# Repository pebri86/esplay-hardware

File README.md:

# esplay-hardware
ESP32 Device which can emulate game and other purpose, has display, button input, sdcard slot, built-in li-ion charger, pcm 5102 DAC module.

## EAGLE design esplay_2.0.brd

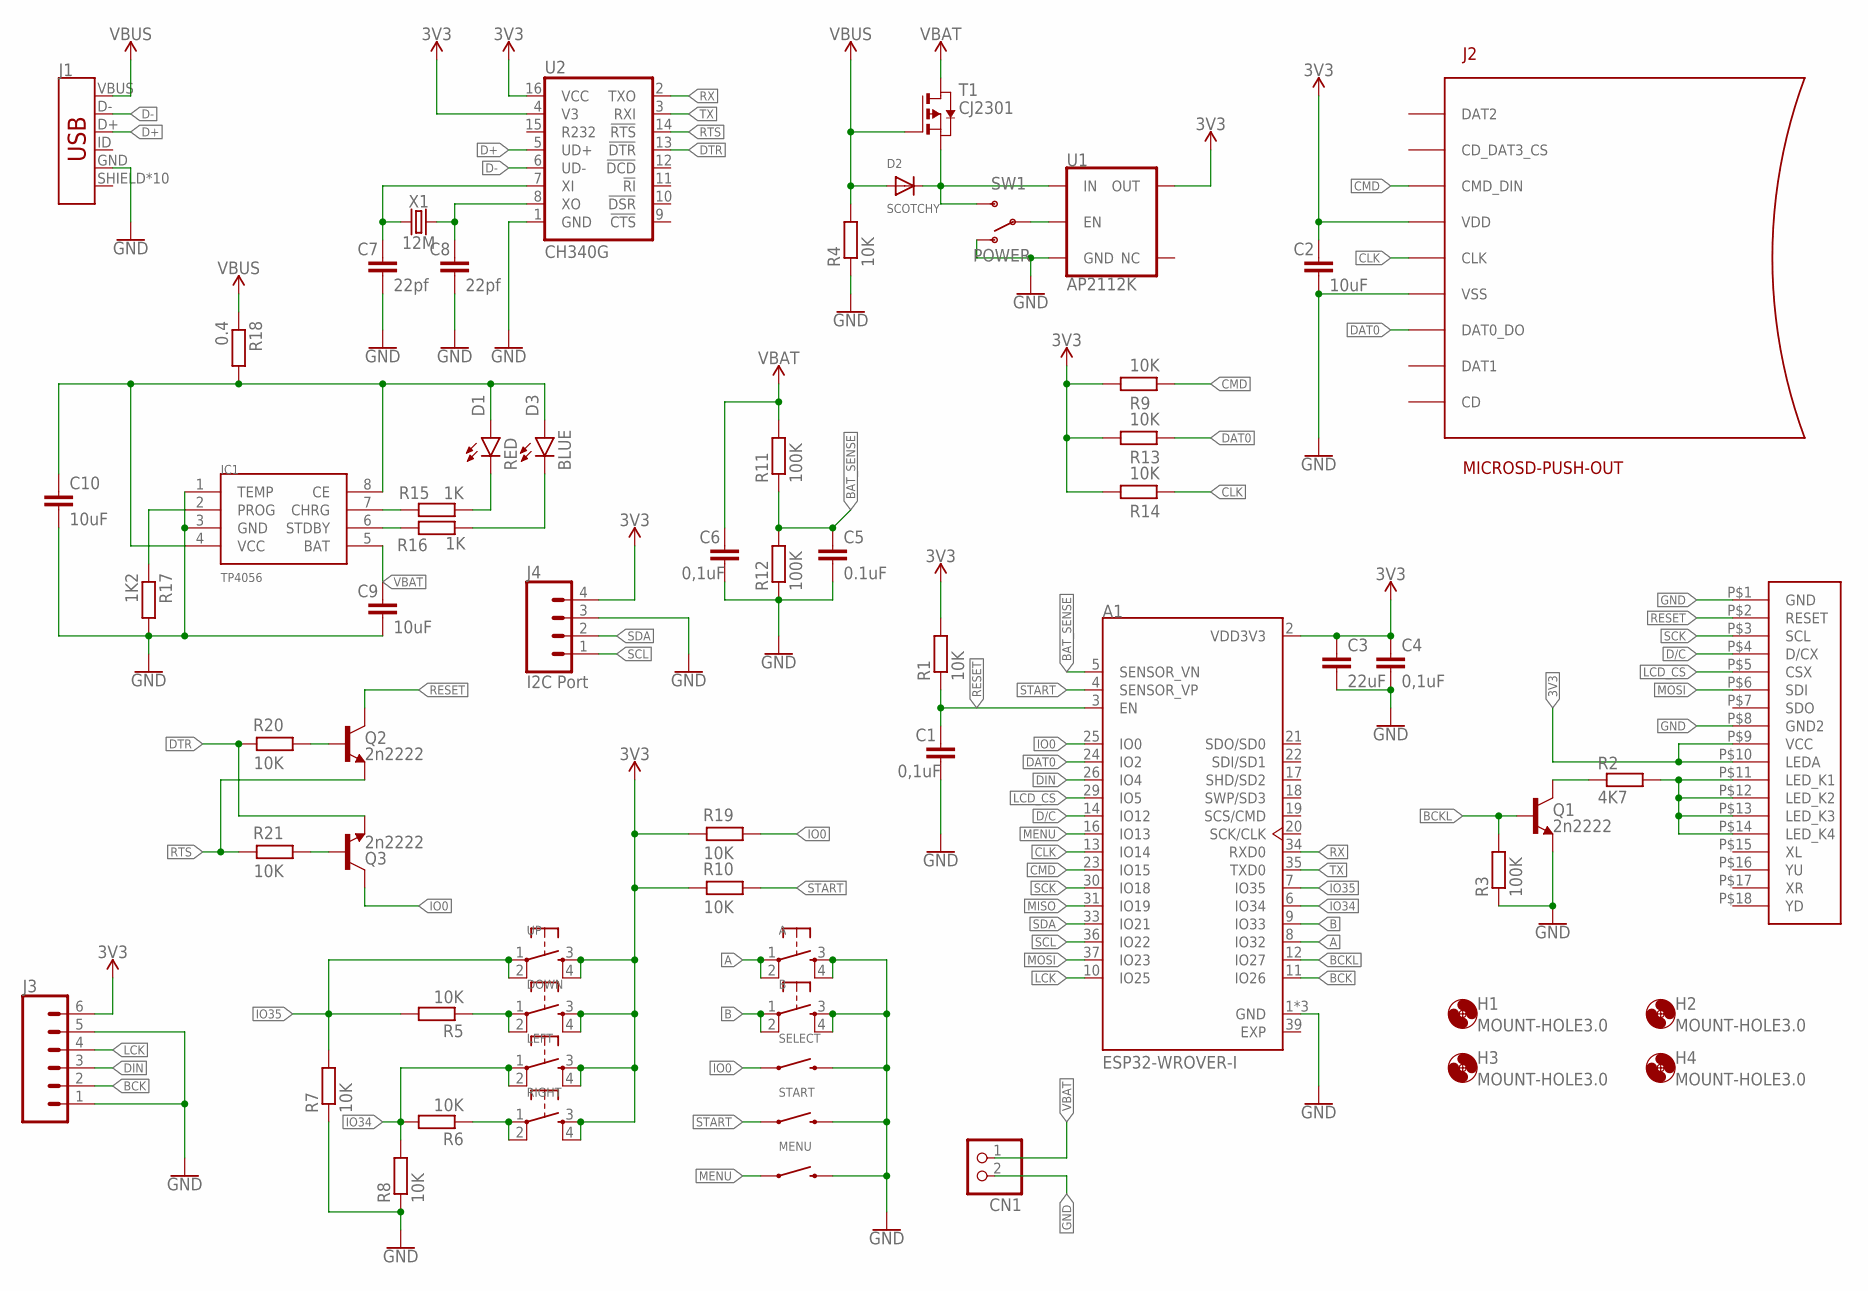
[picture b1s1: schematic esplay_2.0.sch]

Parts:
A: MOMENTARY-SWITCH-SPST-2-SMD-5.2MM; TACTILE_SWITCH_SMD_5.2MM
A1: ESP32-WROVER-I; XCVR_ESP32-WROVER-I
B: MOMENTARY-SWITCH-SPST-2-SMD-5.2MM; TACTILE_SWITCH_SMD_5.2MM
C1, C4, C6: 0,1uF; C0805
C2, C9, C10: 10uF; C0805
C3: 22uF; C0805
C5: 0.1uF; C0805
C7, C8: 22pf; C0805
CN1: JST_2PIN-SMT-RA; JST-PH-2-SMT-RA
D1: RED; LED-0603
D2: SCOTCHY; SMADIODE
D3: BLUE; LED-0603
DOWN: MOMENTARY-SWITCH-SPST-2-SMD-5.2MM; TACTILE_SWITCH_SMD_5.2MM
H1, H2, H3, H4: MOUNT-HOLE3.0; 3,0
IC1: TP4056; SOP-8
J1: USB_MICRO-B_HALF_PTH_MILL; USB-MICROB-PTH-MILL
J2: MICROSD-PUSH-OUT
J3: CONN_06LOCK; 1X06_LOCK
J4: I2C Port; JST-4-PTH
LEFT: MOMENTARY-SWITCH-SPST-2-SMD-5.2MM; TACTILE_SWITCH_SMD_5.2MM
MENU: MOMENTARY-SWITCH-SPST-SMD-6.0X3.5MM; TACTILE_SWITCH_SMD_6.0X3.5MM
Q1, Q2, Q3: 2n2222; SOT23-3
R1, R4, R5, R6, R7, R8, R9, R10, R13, R14, R19, R20, R21: 10K; R0805
R2: 4K7; R0805
R3, R11, R12: 100K; R0805
R15, R16: 1K; R0805
R17: 1K2; R0805
R18: 0.4; R0805
RIGHT: MOMENTARY-SWITCH-SPST-2-SMD-5.2MM; TACTILE_SWITCH_SMD_5.2MM
SELECT: MOMENTARY-SWITCH-SPST-SMD-6.0X3.5MM; TACTILE_SWITCH_SMD_6.0X3.5MM
START: MOMENTARY-SWITCH-SPST-SMD-6.0X3.5MM; TACTILE_SWITCH_SMD_6.0X3.5MM
SW1: POWER; KPS-1290
T1: CJ2301; SOT-23
TFT_DISPLAY: ILI9341-2.4
U1: AP2112K; SOT23-5
U2: CH340G; SO016
UP: MOMENTARY-SWITCH-SPST-2-SMD-5.2MM; TACTILE_SWITCH_SMD_5.2MM
X1: 12M; CRYSTAL-SMD-2X6-CYL

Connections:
3V3: A1.2 (VDD3V3), C2.1, C3.1, C4.1, DOWN.3, DOWN.4, J2.4 (VDD), J3.6, J4.4, LEFT.3, LEFT.4, R1.2, R9.1, R10.2, R13.1, R14.1, R19.2, RIGHT.3, RIGHT.4, TFT_DISPLAY.P$9 (VCC), TFT_DISPLAY.P$10 (LEDA), U1.5 (OUT), U2.4 (V3), U2.16 (VCC), UP.3, UP.4
A: A.1, A.2, A1.8 (IO32)
B: A1.9 (IO33), B.1, B.2
BAT_SENSE: A1.5 (SENSOR_VN), C5.1, R11.1, R12.2
BCK: A1.11 (IO26), J3.2
BCKL: A1.12 (IO27), Q1.1 (B), R3.2
CLK: A1.13 (IO14), J2.5 (CLK), R14.2
CMD: A1.23 (IO15), J2.3 (CMD_DIN), R9.2
D+: J1.D+, U2.5 (UD+)
D-: J1.D-, U2.6 (UD-)
D/C: A1.14 (IO12), TFT_DISPLAY.P$4 (D/CX)
DAT0: A1.24 (IO2), J2.7 (DAT0_DO), R13.2
DIN: A1.26 (IO4), J3.3
DTR: Q3.2 (E), R20.2, U2.13 (!DTR)
EXP: A1.39 (EXP)
GND: A.3, A.4, A1.1 (GND), A1.15 (GND), A1.38 (GND), B.3, B.4, C1.2, C2.2, C3.2, C4.2, C5.2, C6.2, C7.2, C8.2, C9.2, C10.2, CN1.2 (1), IC1.1 (TEMP), IC1.3 (GND), J1.GND, J2.6 (VSS), J2.G1 (VSS), J2.G2 (VSS), J2.G3 (VSS), J2.G4 (VSS), J3.1, J3.5, J4.3, MENU.2, Q1.2 (E), R3.1, R4.1, R7.1, R8.1, R12.1, R17.2, SELECT.2, START.2, SW1.O, TFT_DISPLAY.P$1 (GND), TFT_DISPLAY.P$8 (GND2), U1.2 (GND), U2.1 (GND)
IO0: A1.25 (IO0), Q3.3 (C), R19.1, SELECT.1
IO34: A1.6 (IO34), LEFT.1, LEFT.2, R6.2, R8.2
IO35: A1.7 (IO35), R5.2, R7.2, UP.1, UP.2
LCD_CS: A1.29 (IO5), TFT_DISPLAY.P$5 (CSX)
LCK: A1.10 (IO25), J3.4
MENU: A1.16 (IO13), MENU.1
MISO: A1.31 (IO19)
MOSI: A1.37 (IO23), TFT_DISPLAY.P$6 (SDI)
unnamed: D2.C, SW1.S, T1.2 (S), U1.1 (IN)
unnamed: R2.2, TFT_DISPLAY.P$11 (LED_K1), TFT_DISPLAY.P$12 (LED_K2), TFT_DISPLAY.P$13 (LED_K3), TFT_DISPLAY.P$14 (LED_K4)
unnamed: SW1.P, U1.3 (EN)
unnamed: Q1.3 (C), R2.1
unnamed: C7.1, U2.7 (XI), X1.X1 (1)
unnamed: C8.1, U2.8 (XO), X1.X2 (2)
unnamed: R6.1, RIGHT.1, RIGHT.2
unnamed: DOWN.1, DOWN.2, R5.1
unnamed: IC1.2 (PROG), R17.1
unnamed: IC1.7 (CHRG), R15.2
unnamed: IC1.6 (STDBY), R16.2
unnamed: D1.C, R15.1
unnamed: D3.C, R16.1
unnamed: C10.1, D1.A, D3.A, IC1.4 (VCC), IC1.8 (CE), R18.2
unnamed: Q2.1 (B), R20.1
unnamed: Q3.1 (B), R21.1
RESET: A1.3 (EN), C1.1, Q2.3 (C), R1.1, TFT_DISPLAY.P$2 (RESET)
RTS: Q2.2 (E), R21.2, U2.14 (!RTS)
RX: A1.34 (RXD0), U2.2 (TXO)
SCK: A1.30 (IO18), TFT_DISPLAY.P$3 (SCL)
SCL: A1.36 (IO22), J4.1
SDA: A1.33 (IO21), J4.2
START: A1.4 (SENSOR_VP), R10.1, START.1
TX: A1.35 (TXD0), U2.3 (RXI)
VBAT: C6.1, C9.1, CN1.1 (2), IC1.5 (BAT), R11.2, T1.1 (D)
VBUS: D2.A, J1.VBUS, R4.2, R18.1, T1.3 (G)

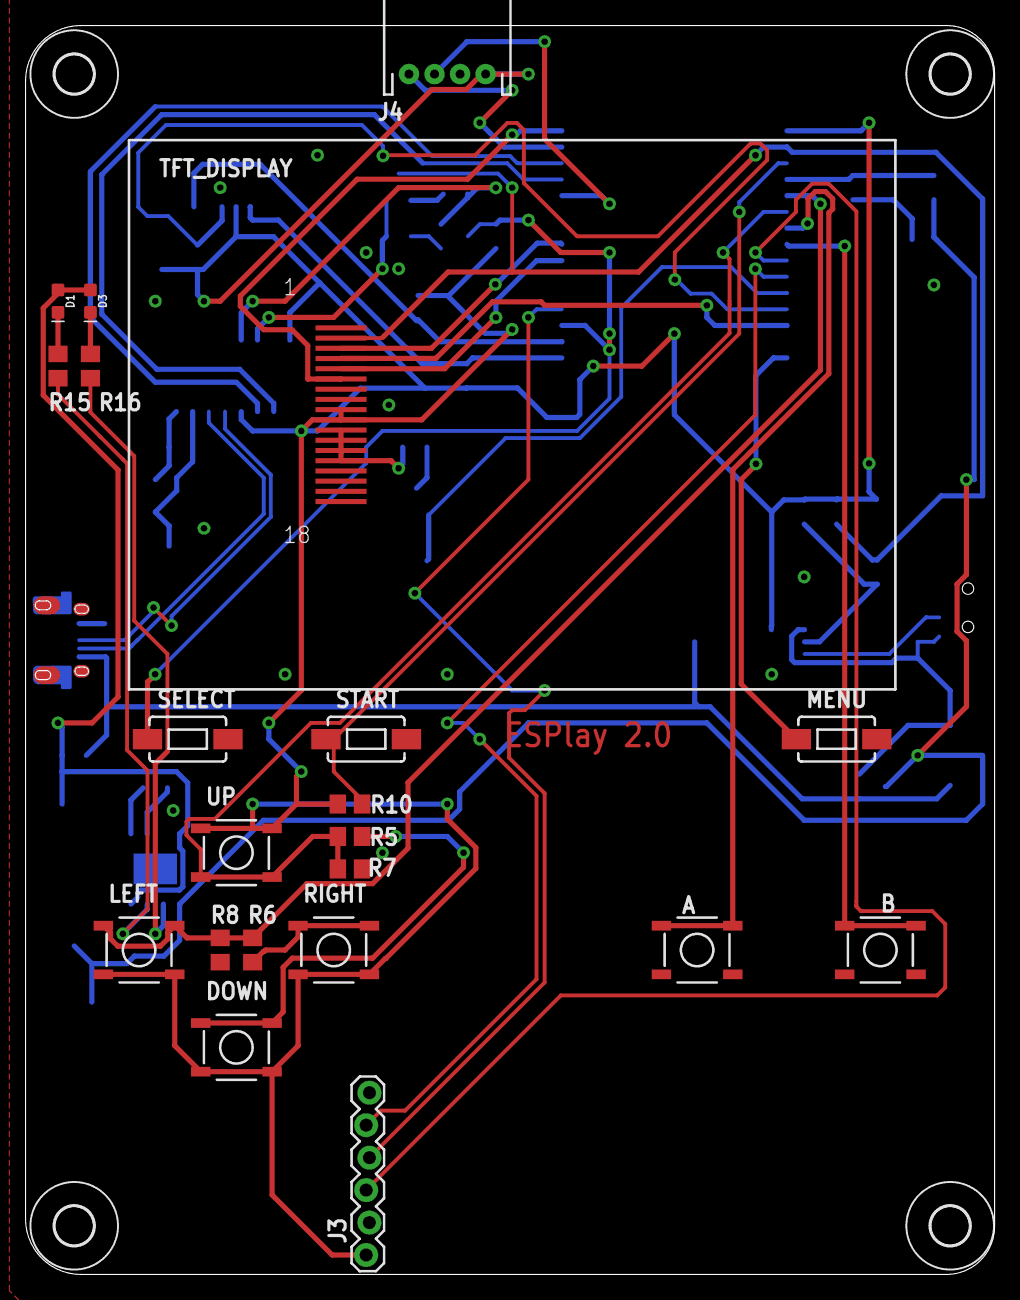
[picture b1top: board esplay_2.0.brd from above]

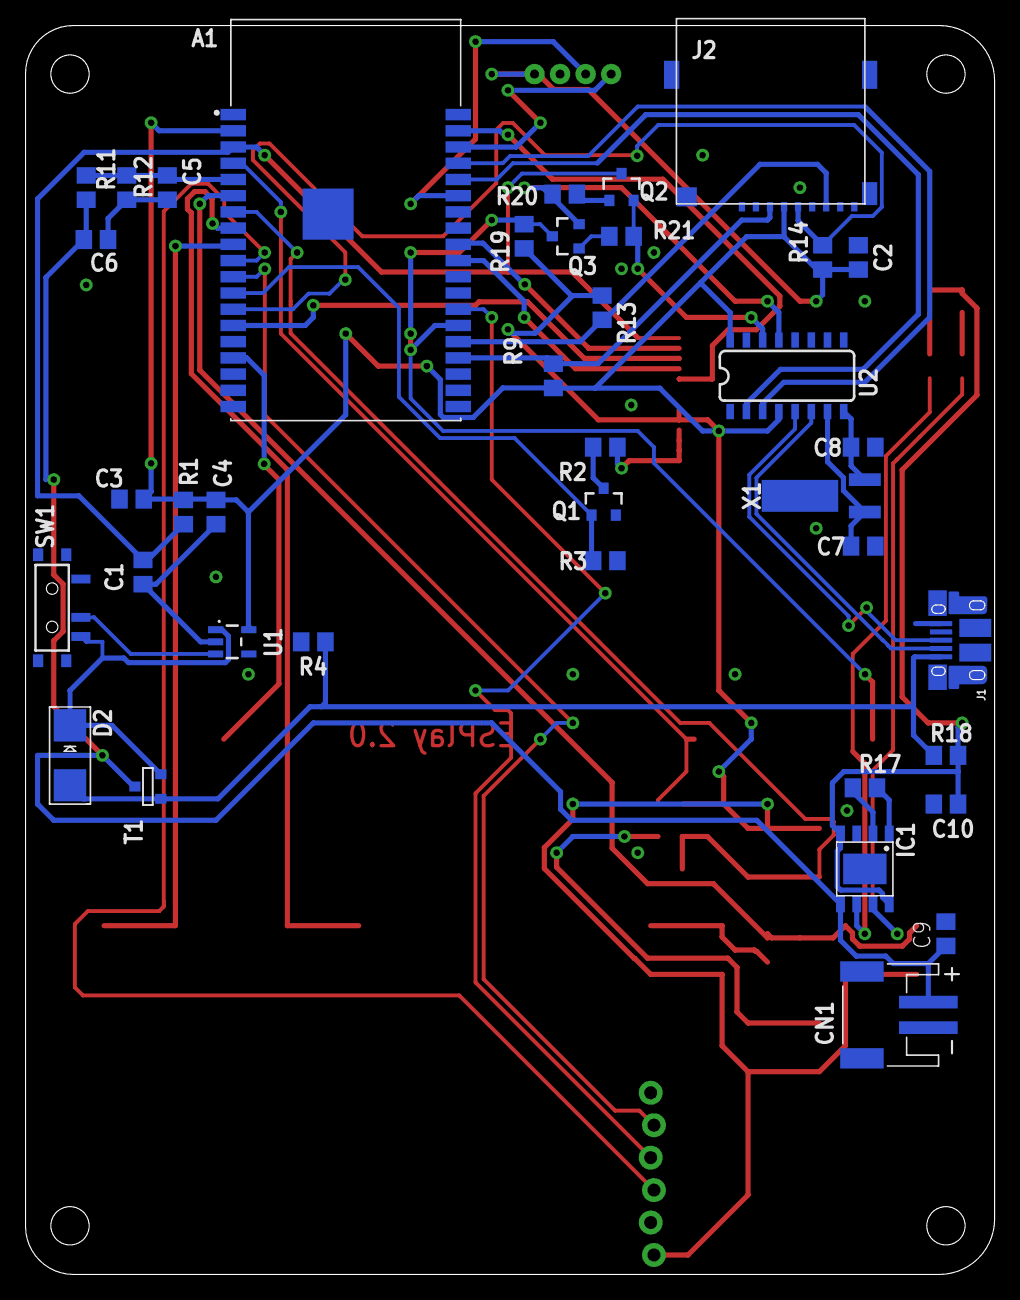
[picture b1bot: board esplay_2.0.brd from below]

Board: 2 copper layers, 75.9 x 97.8 mm, 63 parts (38 on the bottom side), 48 nets.

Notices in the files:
parts and their libraries:
SparkFun-DiscreteSemi: Licensing: Creative Commons ShareAlike 4.0 International - https://creativecommons.org/licenses/by-sa/4.0
